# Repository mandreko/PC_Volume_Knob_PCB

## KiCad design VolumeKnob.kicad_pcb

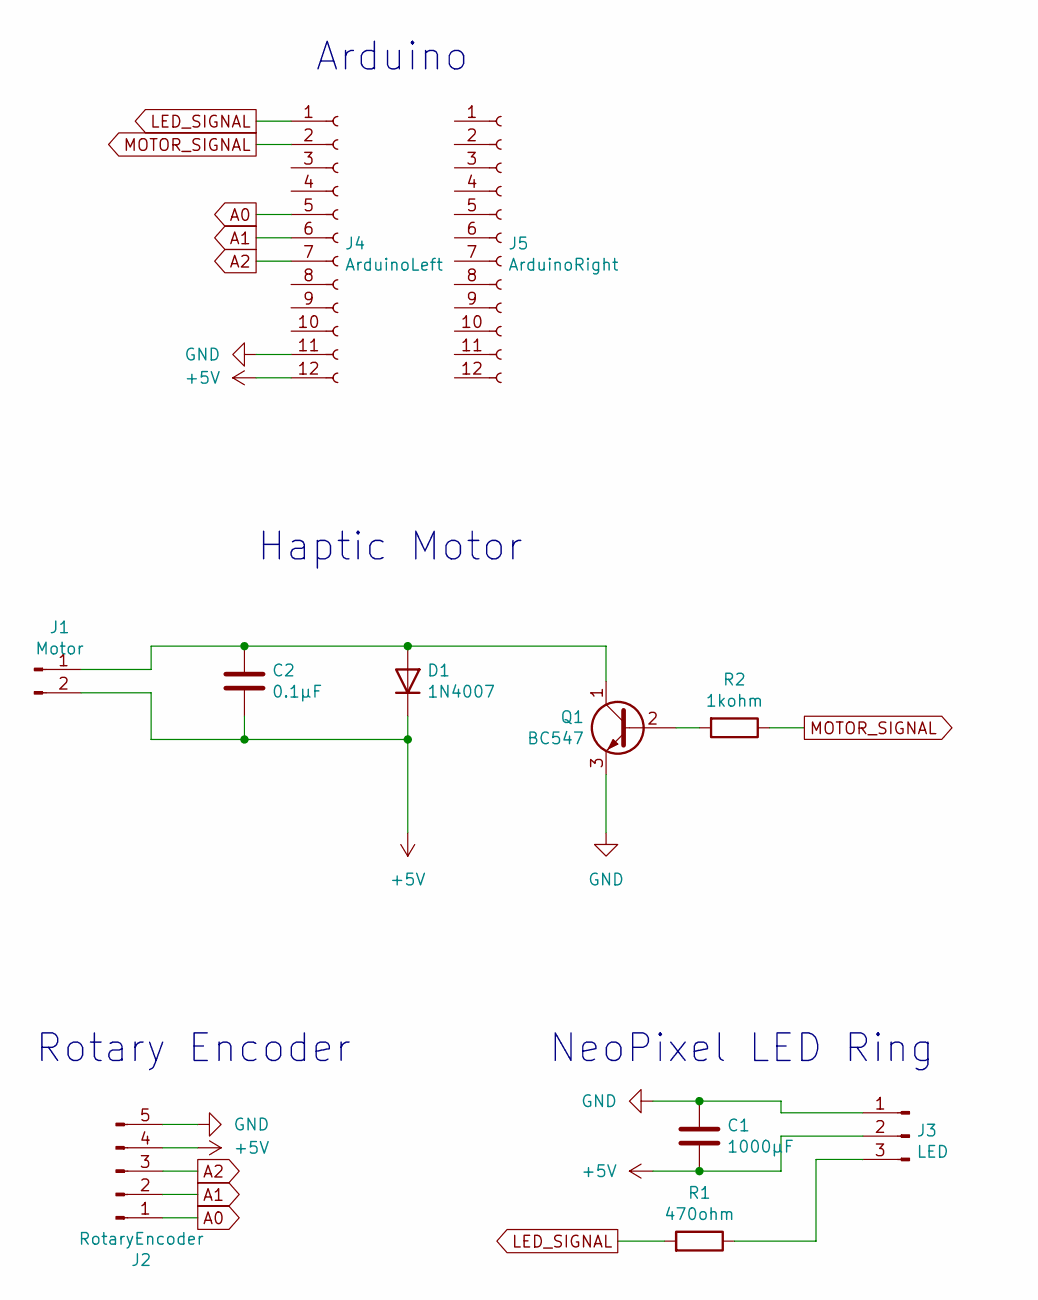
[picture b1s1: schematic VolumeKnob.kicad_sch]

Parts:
C1: 1000µF; CP_Radial_D10.0mm_P5.00mm
C2: 0.1µF; C_Disc_D3.8mm_W2.6mm_P2.50mm
D1: 1N4007; D_DO-41_SOD81_P10.16mm_Horizontal
J1: Motor; PinHeader_1x02_P2.54mm_Horizontal
J2: RotaryEncoder; PinHeader_1x05_P2.54mm_Horizontal
J3: LED; PinHeader_1x03_P2.54mm_Horizontal
J4: ArduinoLeft; PinHeader_1x12_P2.54mm_Vertical
J5: ArduinoRight; PinHeader_1x12_P2.54mm_Vertical
Q1: BC547; TO-92_Inline
R1: 470ohm; R_Axial_DIN0411_L9.9mm_D3.6mm_P15.24mm_Horizontal
R2: 1kohm; R_Axial_DIN0411_L9.9mm_D3.6mm_P15.24mm_Horizontal

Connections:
+5V: C1.2, C2.2, D1.1 (K), J1.2, J2.4, J3.2, J4.12
A0: J2.1, J4.5
A1: J2.2, J4.6
A2: J2.3, J4.7
GND: C1.1, J2.5, J3.1, J4.11, Q1.3 (E)
LED_SIGNAL: J4.1, R1.2
MOTOR_SIGNAL: J4.2, R2.1
unnamed: C2.1, D1.2 (A), J1.1, Q1.1 (C)
unnamed: Q1.2 (B), R2.2
unnamed: J3.3, R1.1

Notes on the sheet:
NeoPixel LED Ring
Haptic Motor
Rotary Encoder
Arduino

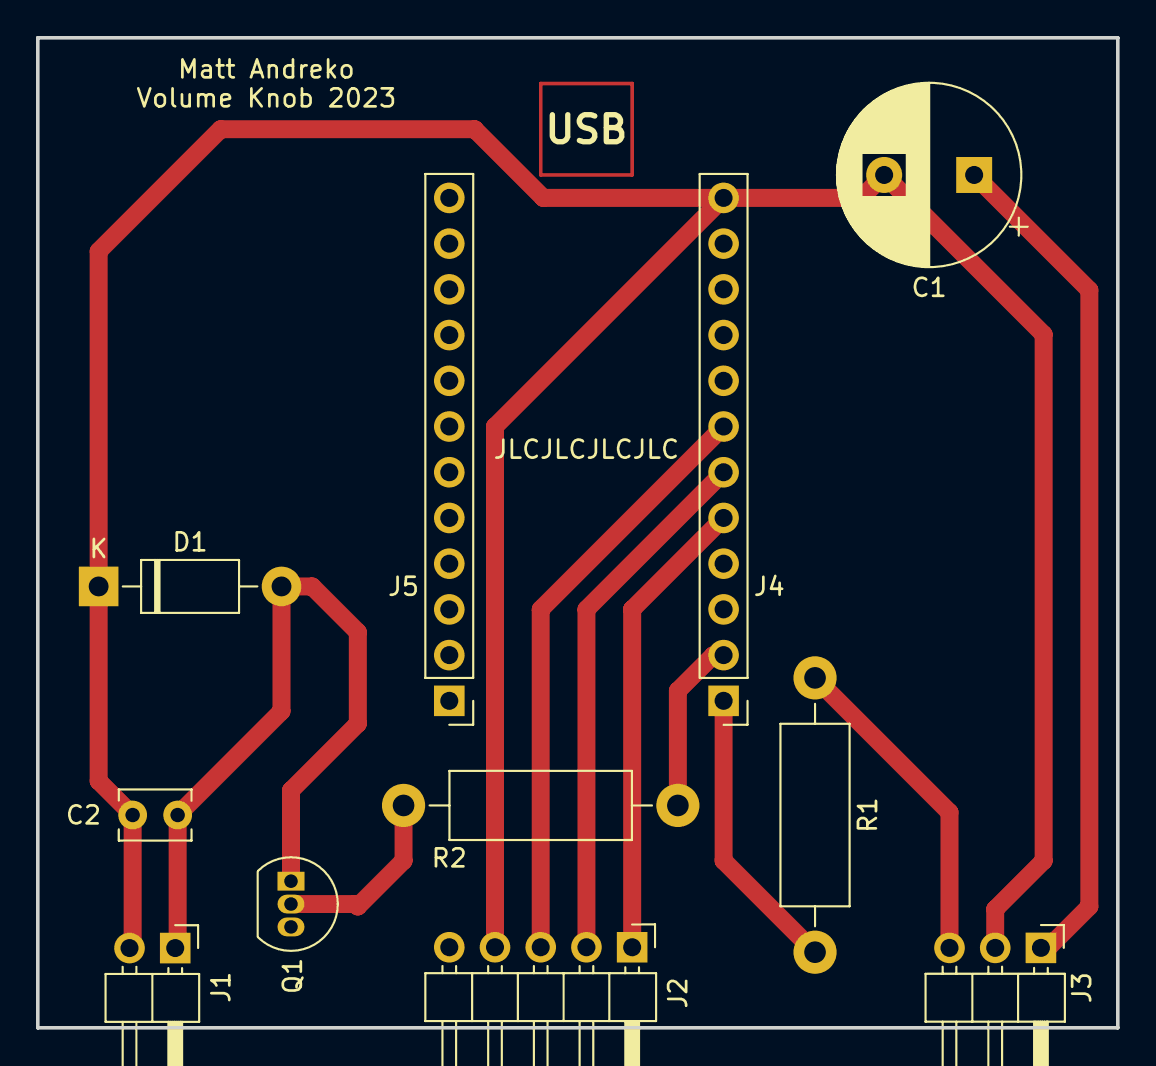
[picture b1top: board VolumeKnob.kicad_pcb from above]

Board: 2 copper layers, 60.0 x 55.0 mm, 11 parts (0 on the bottom side), 10 nets.
